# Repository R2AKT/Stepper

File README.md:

License addendum - https://github.com/R2AKT/Stepper/blob/main/Addendum.txt
# Stepper

Debug module. For Mega-80 (Mega-580) DIY 8-bit micro-computer - https://github.com/R2AKT/Mega-80.

Allows you to execute the program in step-by-step mode, displaying the states of the address and data buses.
Using the boot module, you can read and write data from/to memory - https://github.com/R2AKT/8080-5-CI.

Status: tested.

Модуль отладки. Для самодельной 8-битной микро-ЭВМ - https://github.com/R2AKT/Mega-80.

Позволяет выполнять программу в пошаговом режиме, с отображением состояний шины адреса и данных.
С помощью модуля загрузки позволяет считывать и записывать данные из/в память - https://github.com/R2AKT/8080-5-CI.

Статус: проверена.

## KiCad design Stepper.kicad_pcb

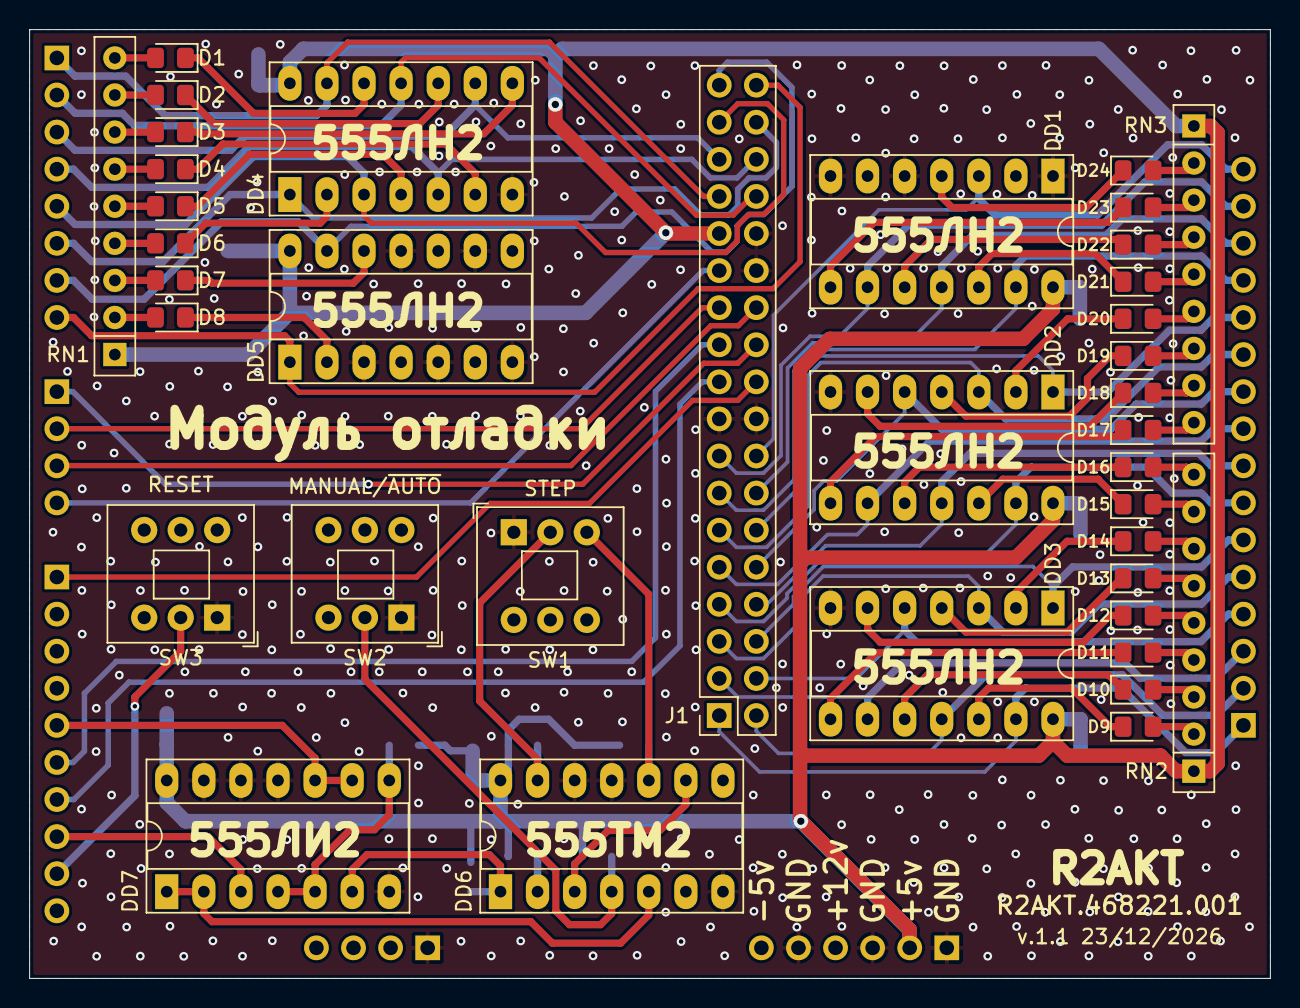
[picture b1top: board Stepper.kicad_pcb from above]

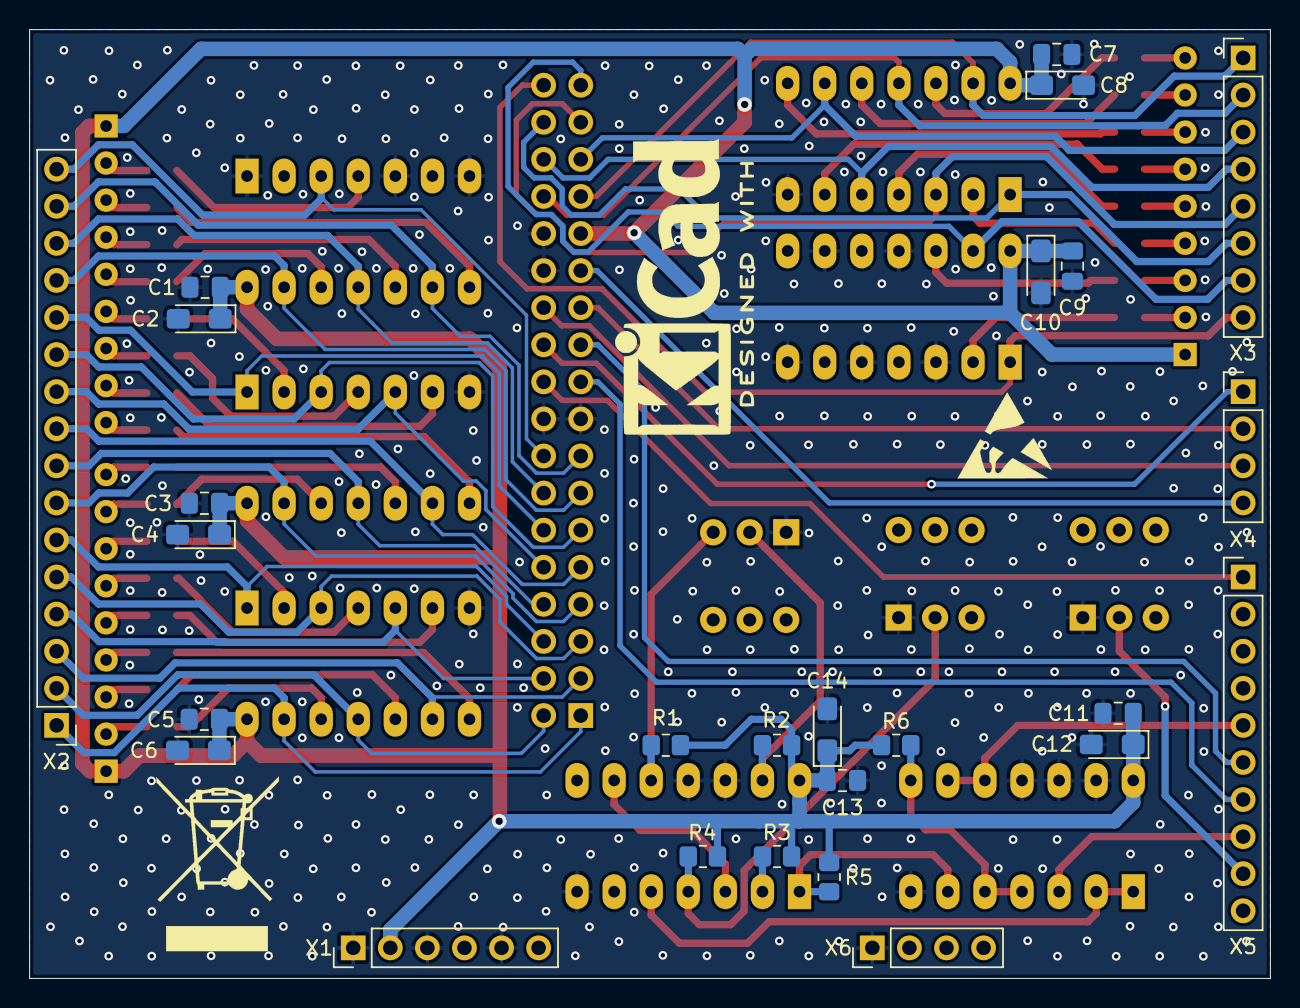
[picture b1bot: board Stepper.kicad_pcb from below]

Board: 2 copper layers, 85.0 x 65.0 mm, 64 parts (26 on the bottom side), 92 nets.

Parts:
C1, C3, C5, C7, C9, C11, C13: 100n; C_0805_2012Metric_Pad1.18x1.45mm_HandSolder
C2, C4, C6, C8, C10, C12, C14: 1u; CP_EIA-3216-18_Kemet-A_Pad1.58x1.35mm_HandSolder
D1, D2, D3, D4, D5, D6, D7, D8, D9, D10, D11, D12, D13, D14, D15, D16, D17, D18, D19, D20, D21, D22, D23, D24: LED; LED_0805_2012Metric_Pad1.15x1.40mm_HandSolder
DD1, DD2, DD3, DD4, DD5: 555ЛН2 (74LS05); DIP-14_W7.62mm_Socket_LongPads
DD6: 555ТМ2 (74LS74); DIP-14_W7.62mm_Socket_LongPads
DD7: 555ЛИ2 (74LS09); DIP-14_W7.62mm_Socket_LongPads
J1: Conn_02x18_Counter_Clockwise; PinSocket_2x18_P2.54mm_Vertical
R1, R2, R3, R4, R5, R6: 1k; R_0805_2012Metric_Pad1.20x1.40mm_HandSolder
RN1, RN2, RN3: 270; R_Array_SIP9
SW1: STEP; SW_Push_2P2T_Toggle_CK_PVA2OAH5xxxxxxV2
SW2: MANUAL/~{AUTO}; SW_Push_2P2T_Toggle_CK_PVA2OAH5xxxxxxV2
SW3: RESET; SW_Push_2P2T_Toggle_CK_PVA2OAH5xxxxxxV2
X1: Power; PinHeader_1x06_P2.54mm_Vertical
X2: Address; PinHeader_1x16_P2.54mm_Vertical
X3: Data; PinHeader_1x08_P2.54mm_Vertical
X4: Mode; PinHeader_1x04_P2.54mm_Vertical
X5: Control; PinHeader_1x10_P2.54mm_Vertical
X6: Clock; PinHeader_1x04_P2.54mm_Vertical

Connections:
/+5V: C1.1, C2.1, C3.1, C4.1, C5.1, C6.1, C7.1, C8.1, C9.1, C10.1, C11.1, C12.1, C13.1, C14.1, DD1.14 (VCC), DD2.14 (VCC), DD3.14 (VCC), DD4.14 (VCC), DD5.14 (VCC), DD6.14 (VCC), DD7.14 (VCC), J1.27, R1.1, R2.1, R3.2, R4.1, R5.1, R6.1, RN1.1 (common), RN2.1 (common), RN3.1 (common), X1.2
/AB0: DD3.13, J1.1, X2.1
/AB1: DD3.11, J1.2, X2.2
/AB2: DD3.9, J1.3, X2.3
/AB3: DD3.5, J1.4, X2.4
/AB4: DD3.3, J1.5, X2.5
/AB5: DD3.1, J1.6, X2.6
/AB6: DD2.13, J1.7, X2.7
/AB7: DD2.11, J1.8, X2.8
/AB8: DD2.9, J1.9, X2.9
/AB9: DD2.5, J1.10, X2.10
/AB10: DD2.3, J1.11, X2.11
/AB11: DD2.1, J1.12, X2.12
/AB12: DD1.13, J1.13, X2.13
/AB13: DD1.11, J1.14, X2.14
/AB14: DD1.9, J1.15, X2.15
/AB15: DD1.3, J1.16, X2.16
/DB0: DD4.13, J1.29, X3.1
/DB1: DD4.11, J1.30, X3.2
/DB2: DD4.9, J1.31, X3.3
/DB3: DD4.5, J1.32, X3.4
/DB4: DD4.3, J1.33, X3.5
/DB5: DD4.1, J1.34, X3.6
/DB6: DD5.13, J1.35, X3.7
/DB7: DD5.1, J1.36, X3.8
/HLDA: J1.21, X5.6
/HRQ: J1.19, X5.7
/LED_A0: D9.1 (K), DD3.12
/LED_A1: D10.1 (K), DD3.10
/LED_A2: D11.1 (K), DD3.8
/LED_A3: D12.1 (K), DD3.6
/LED_A4: D13.1 (K), DD3.4
/LED_A5: D14.1 (K), DD3.2
/LED_A6: D15.1 (K), DD2.12
/LED_A7: D16.1 (K), DD2.10
/LED_A8: D17.1 (K), DD2.8
/LED_A9: D18.1 (K), DD2.6
/LED_A10: D19.1 (K), DD2.4
/LED_A11: D20.1 (K), DD2.2
/LED_A12: D21.1 (K), DD1.12
/LED_A13: D22.1 (K), DD1.10
/LED_A14: D23.1 (K), DD1.8
/LED_A15: D24.1 (K), DD1.4
/LED_D0: D1.1 (K), DD4.12
/LED_D1: D2.1 (K), DD4.10
/LED_D2: D3.1 (K), DD4.8
/LED_D3: D4.1 (K), DD4.6
/LED_D4: D5.1 (K), DD4.4
/LED_D5: D6.1 (K), DD4.2
/LED_D6: D7.1 (K), DD5.12
/LED_D7: D8.1 (K), DD5.2
/WAIT: DD7.9, DD7.10, X5.5
/XRDY: DD7.3, X5.8
/~BUSEN: J1.20, X5.1
/~IOR: J1.23, X4.2
/~IOW: J1.25, X4.4
/~MEMR: J1.22, X4.1
/~MEMW: J1.24, X4.3
/~RESIN: SW3.2 (C), X5.9
GND: C1.2, C2.2, C3.2, C4.2, C5.2, C6.2, C7.2, C8.2, C9.2, C10.2, C11.2, C12.2, C13.2, C14.2, DD1.1, DD1.5, DD1.7 (GND), DD2.7 (GND), DD3.7 (GND), DD4.7 (GND), DD5.3, DD5.5, DD5.7 (GND), DD5.9, DD5.11, DD6.7 (GND), DD6.11 (C), DD6.12 (D), DD7.7 (GND), DD7.11, DD7.12, DD7.13, J1.17, J1.18, J1.26, J1.28, SW1.1 (B), SW2.1 (B), SW3.1 (B), X1.1, X1.3, X1.5, X6.1
unnamed: D1.2 (A), RN1.9 (R8)
unnamed: D2.2 (A), RN1.8 (R7)
unnamed: D3.2 (A), RN1.7 (R6)
unnamed: D4.2 (A), RN1.6 (R5)
unnamed: D5.2 (A), RN1.5 (R4)
unnamed: D6.2 (A), RN1.4 (R3)
unnamed: D7.2 (A), RN1.3 (R2)
unnamed: D8.2 (A), RN1.2 (R1)
unnamed: D9.2 (A), RN2.2 (R1)
unnamed: D10.2 (A), RN2.3 (R2)
unnamed: D11.2 (A), RN2.4 (R3)
unnamed: D12.2 (A), RN2.5 (R4)
unnamed: D13.2 (A), RN2.6 (R5)
unnamed: D14.2 (A), RN2.7 (R6)
unnamed: D15.2 (A), RN2.8 (R7)
unnamed: D16.2 (A), RN2.9 (R8)
unnamed: D17.2 (A), RN3.9 (R8)
unnamed: D18.2 (A), RN3.8 (R7)
unnamed: D19.2 (A), RN3.7 (R6)
unnamed: D20.2 (A), RN3.6 (R5)
unnamed: D21.2 (A), RN3.5 (R4)
unnamed: D22.2 (A), RN3.4 (R3)
unnamed: D23.2 (A), RN3.3 (R2)
unnamed: D24.2 (A), RN3.2 (R1)
unnamed: DD6.3 (C), DD6.9 (Q)
unnamed: DD6.2 (D), R3.1
unnamed: DD6.5 (Q), DD7.1, DD7.2
unnamed: DD6.1 (~R), DD7.6, R5.2
unnamed: DD6.4 (~S), R4.2, SW2.2 (C)
unnamed: DD6.13 (~R), R2.2, SW1.2 (C)
unnamed: DD6.10 (~S), R1.2, SW1.3 (A)
unnamed: DD7.4, DD7.5, DD7.8, R6.2

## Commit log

2026-01-26 Add files via upload
    Fix button error and missed ground.
    Исправлена ошибка кнопок и отсутствующих земель.

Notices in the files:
README.md:
License: MIT
